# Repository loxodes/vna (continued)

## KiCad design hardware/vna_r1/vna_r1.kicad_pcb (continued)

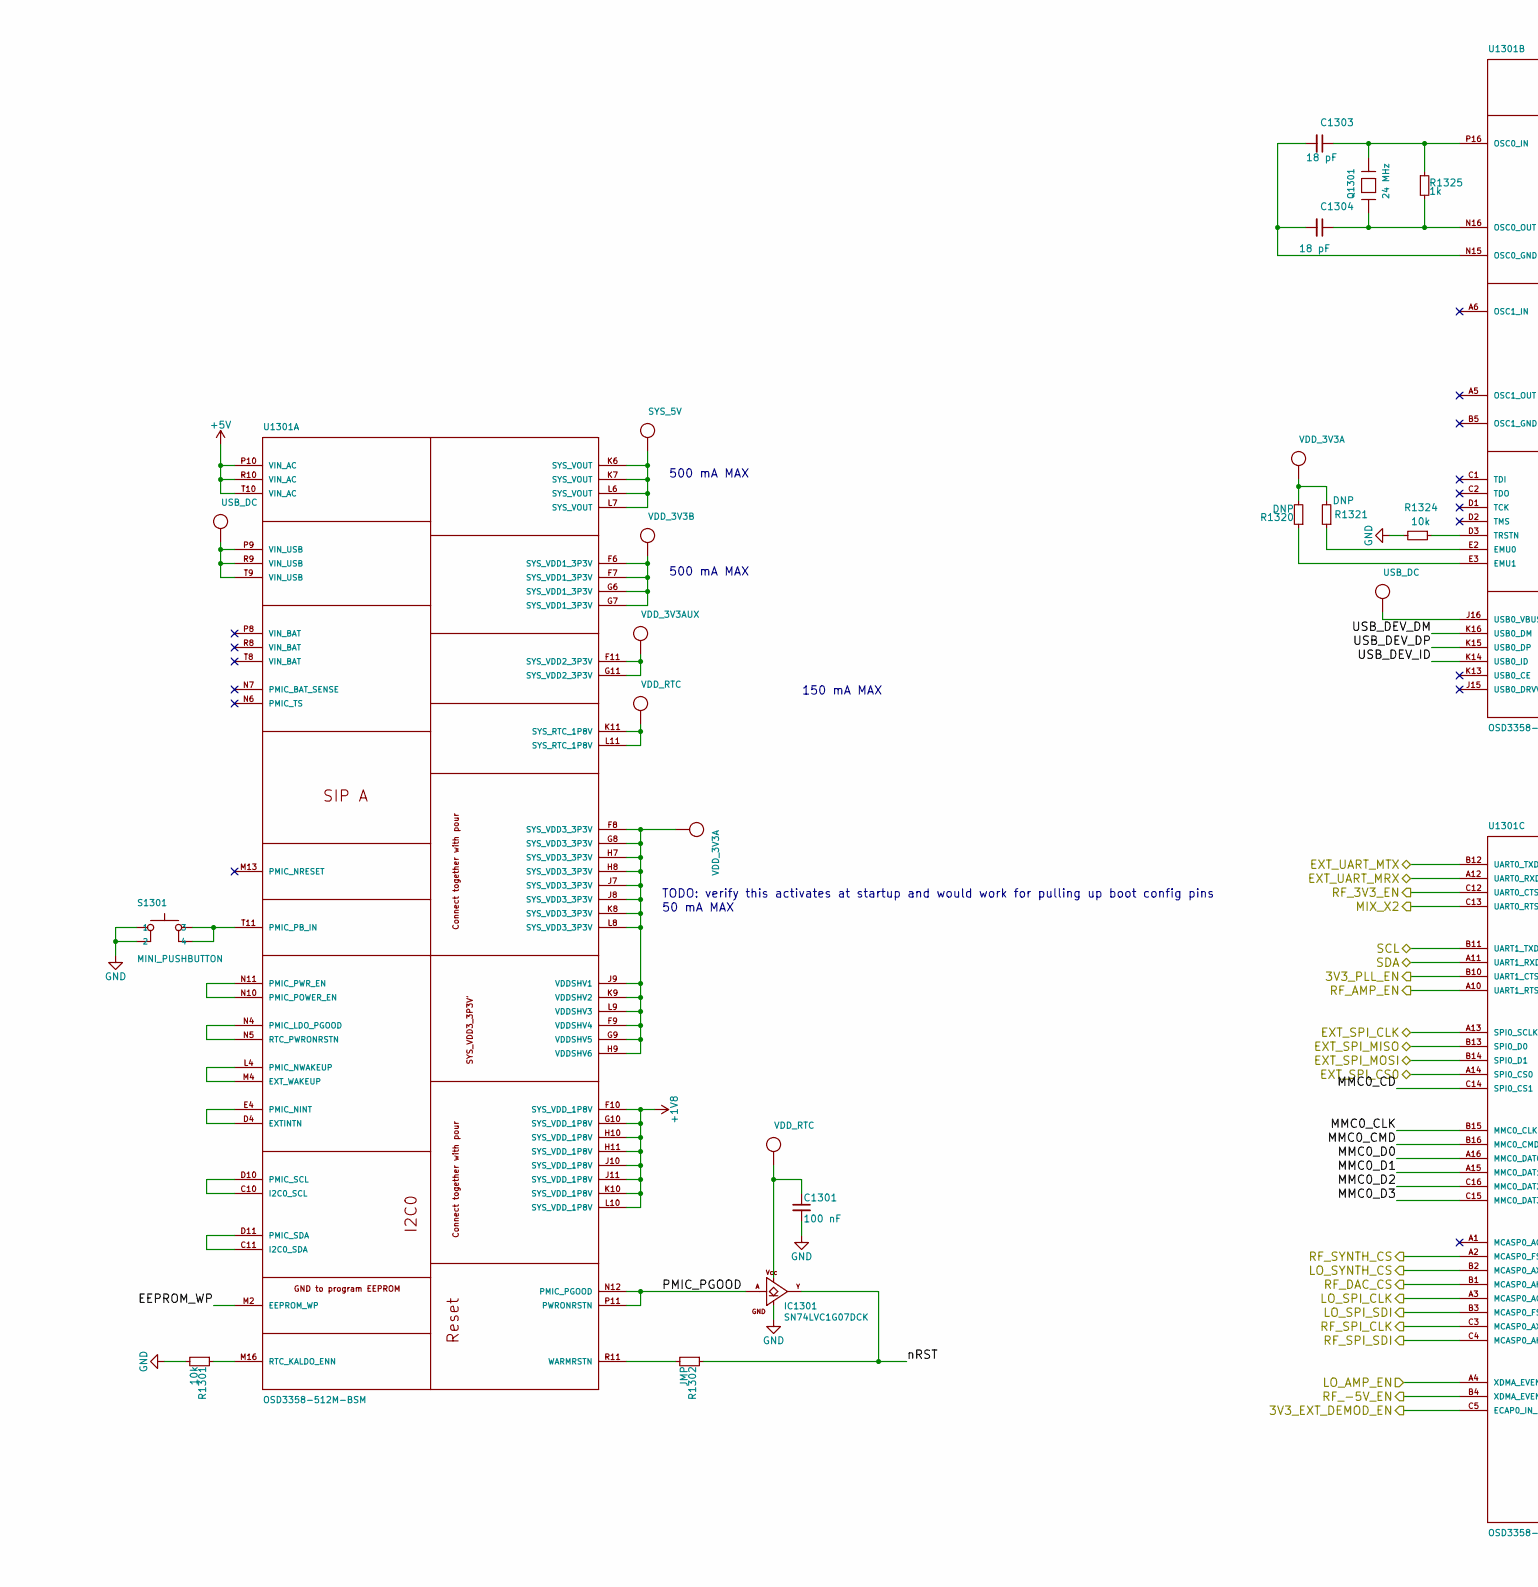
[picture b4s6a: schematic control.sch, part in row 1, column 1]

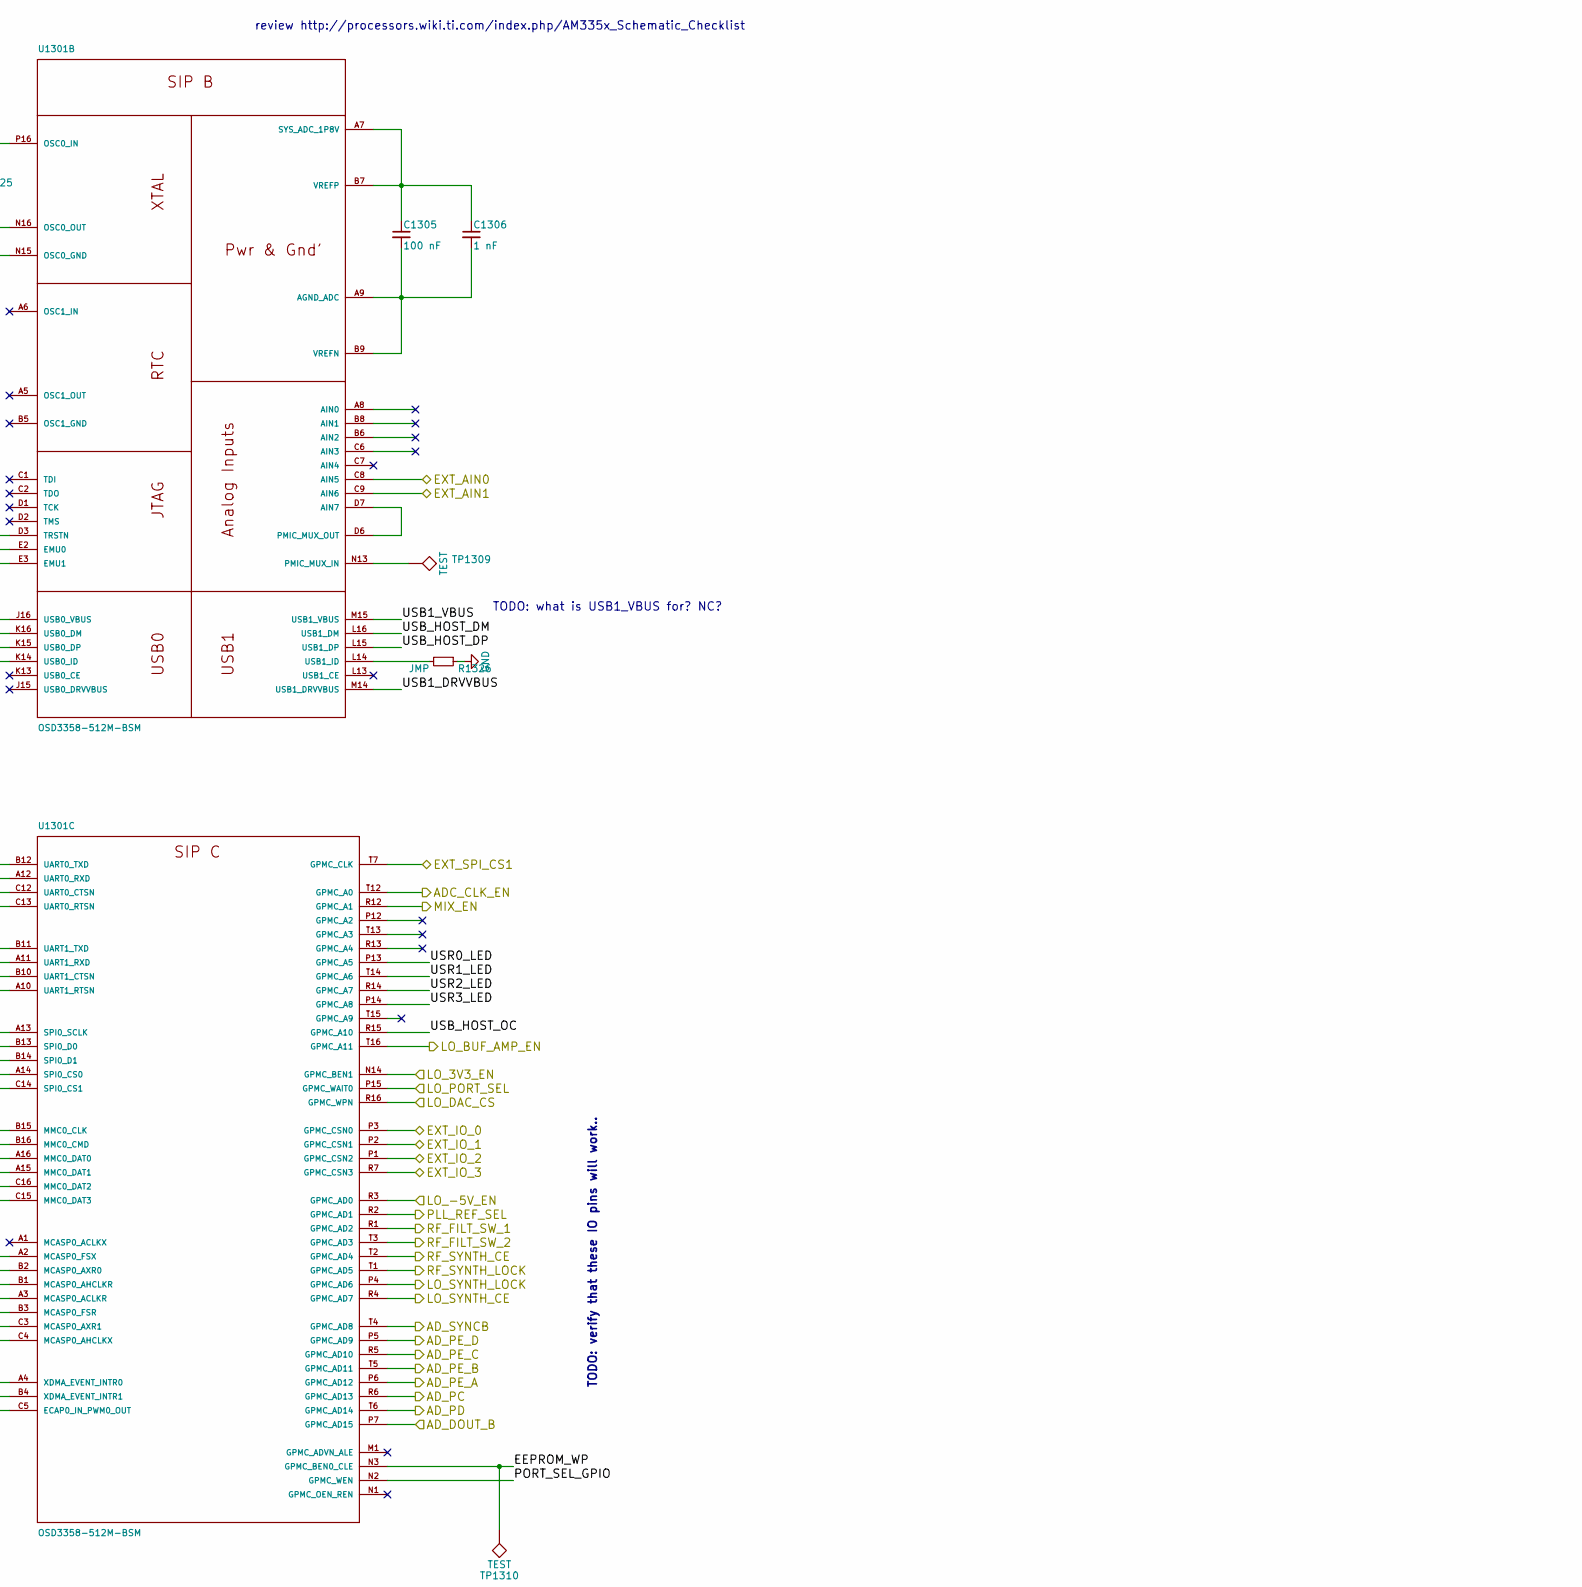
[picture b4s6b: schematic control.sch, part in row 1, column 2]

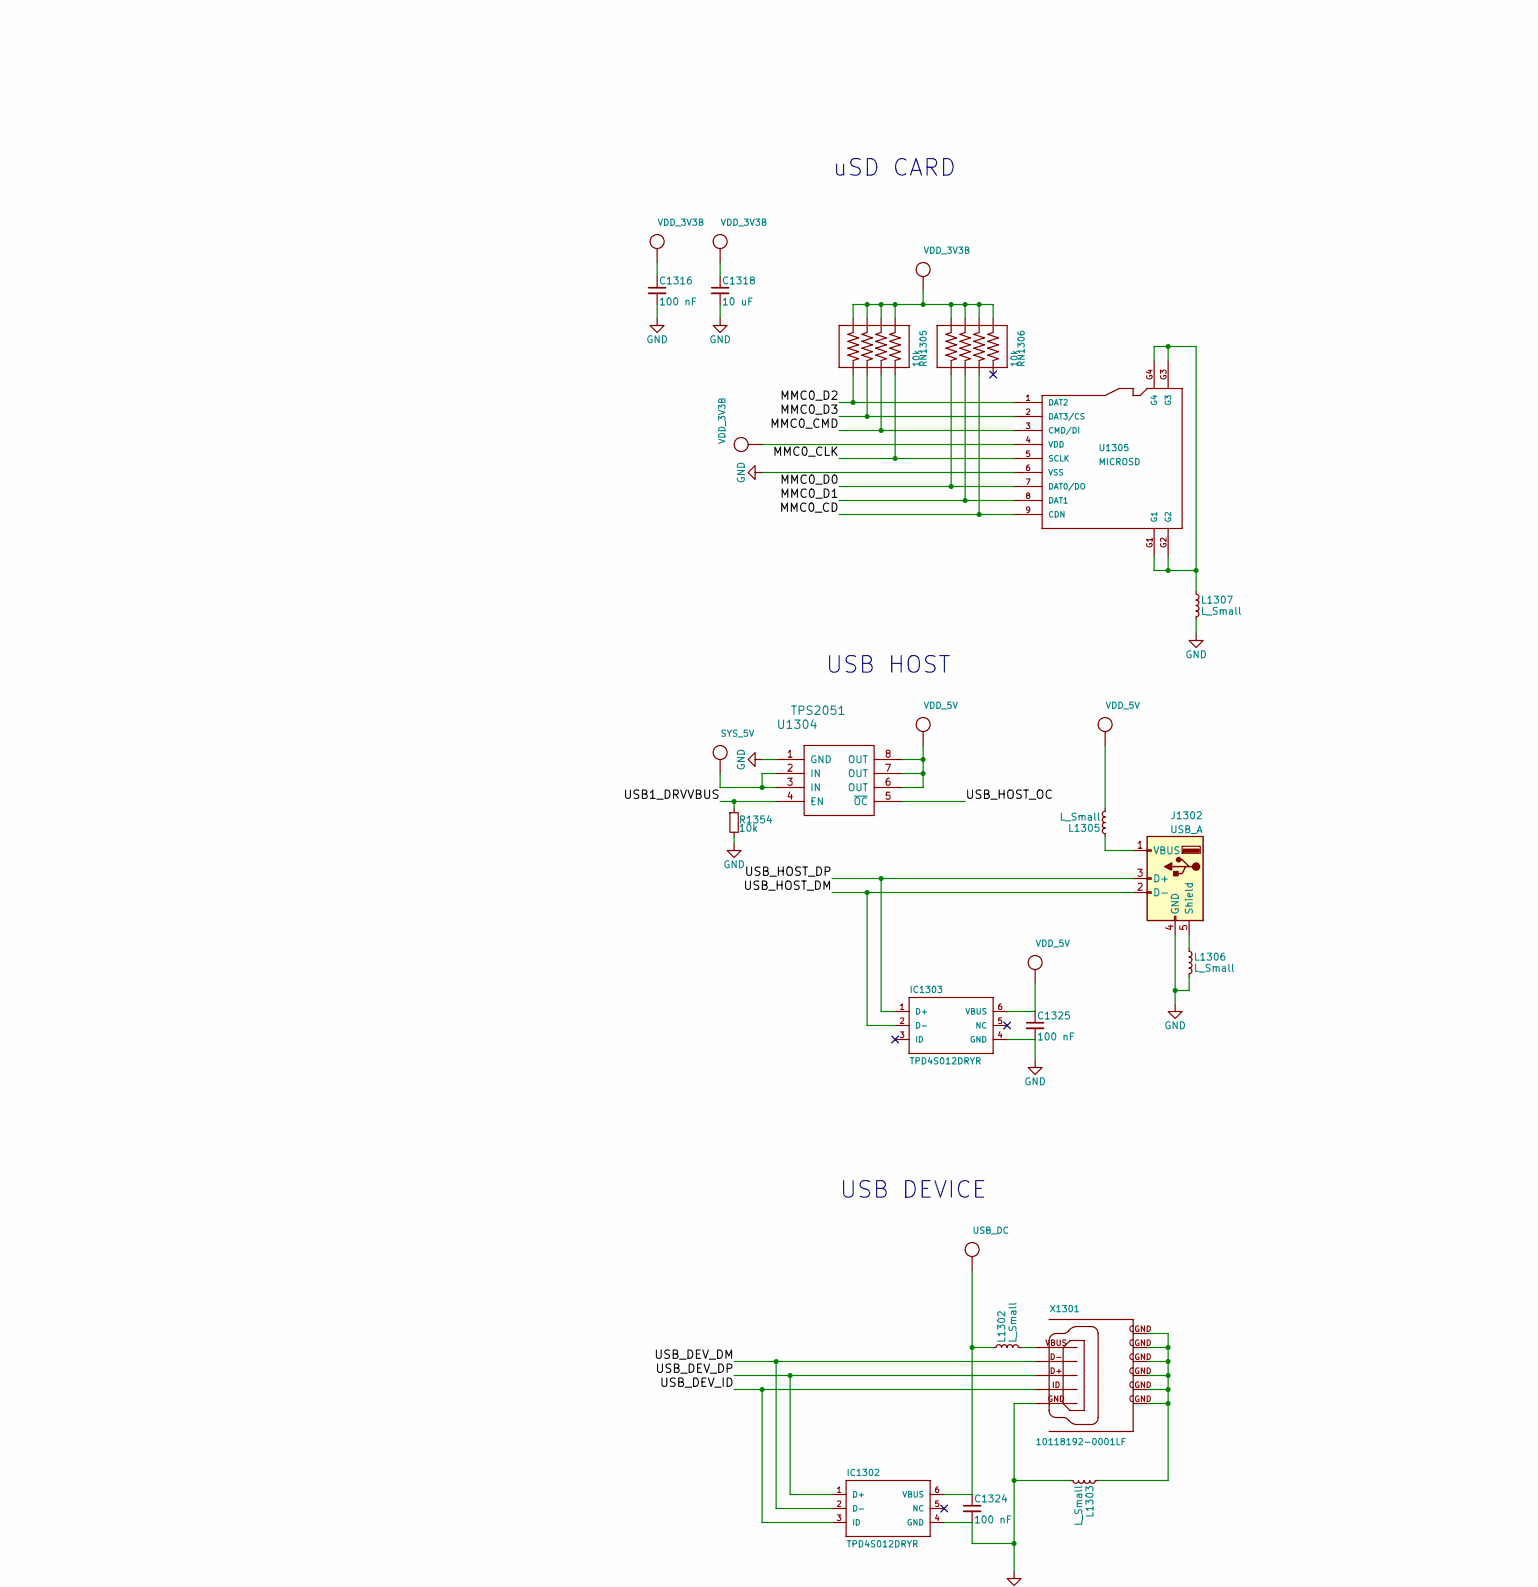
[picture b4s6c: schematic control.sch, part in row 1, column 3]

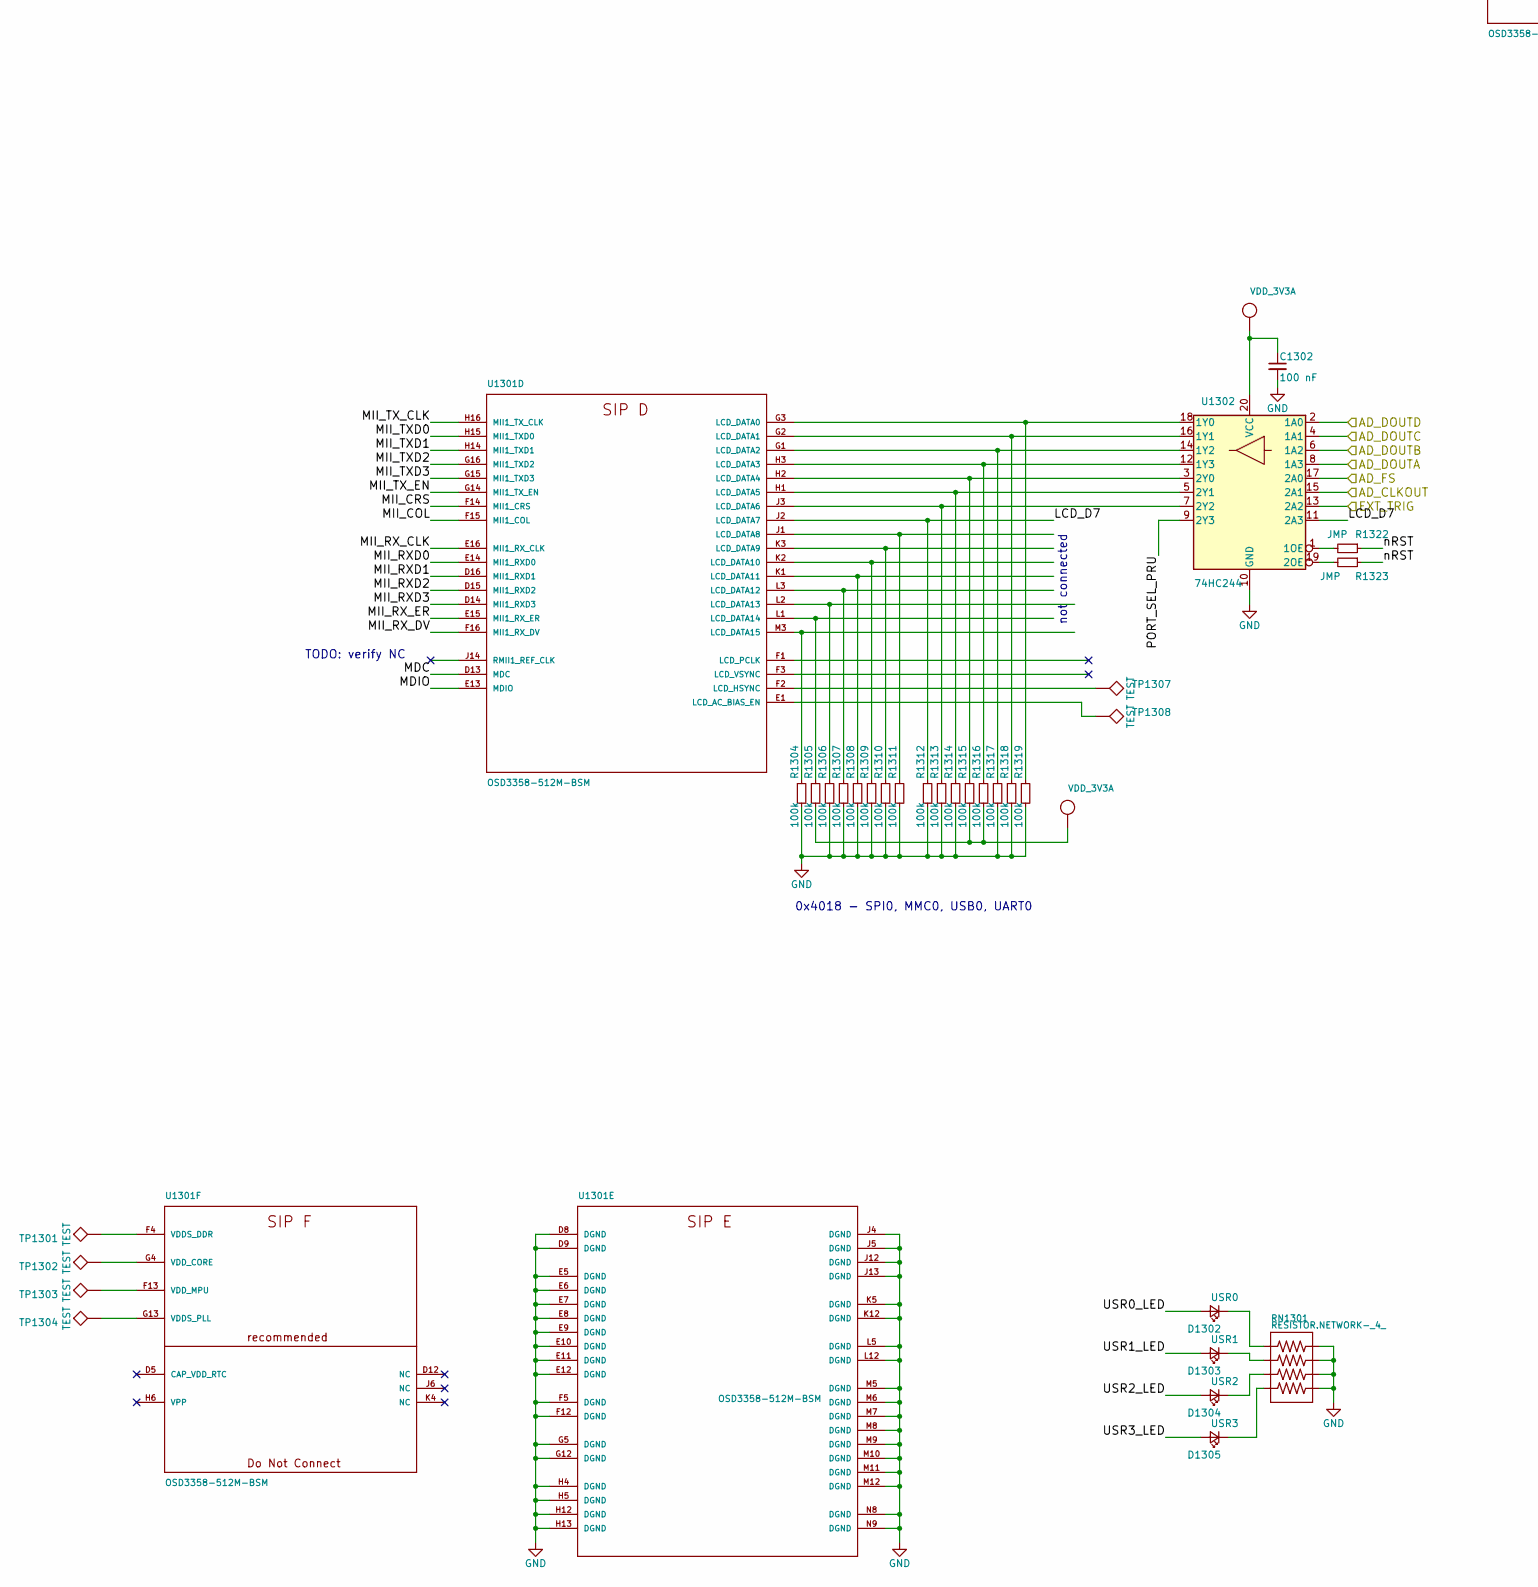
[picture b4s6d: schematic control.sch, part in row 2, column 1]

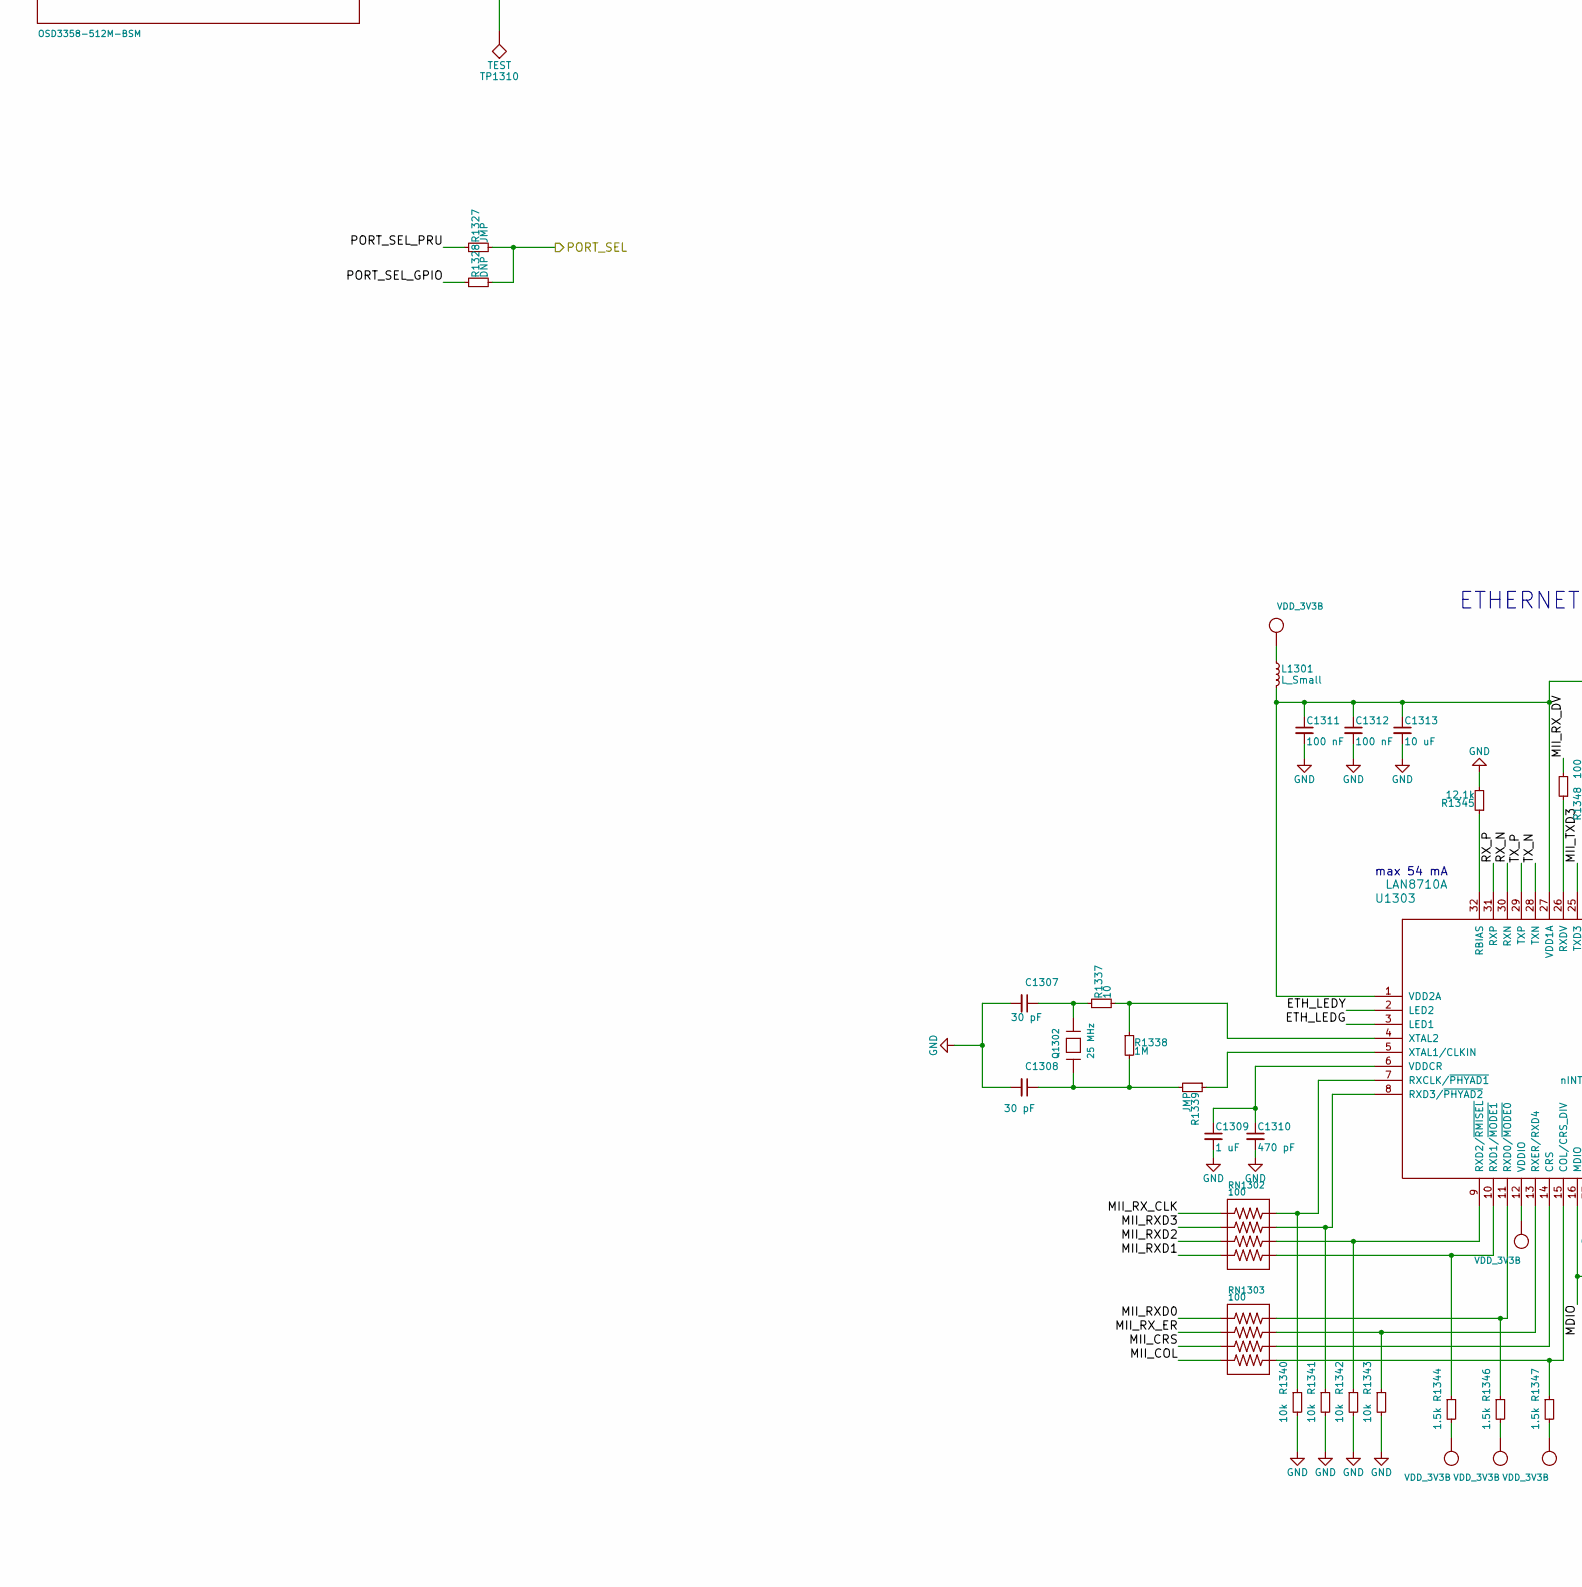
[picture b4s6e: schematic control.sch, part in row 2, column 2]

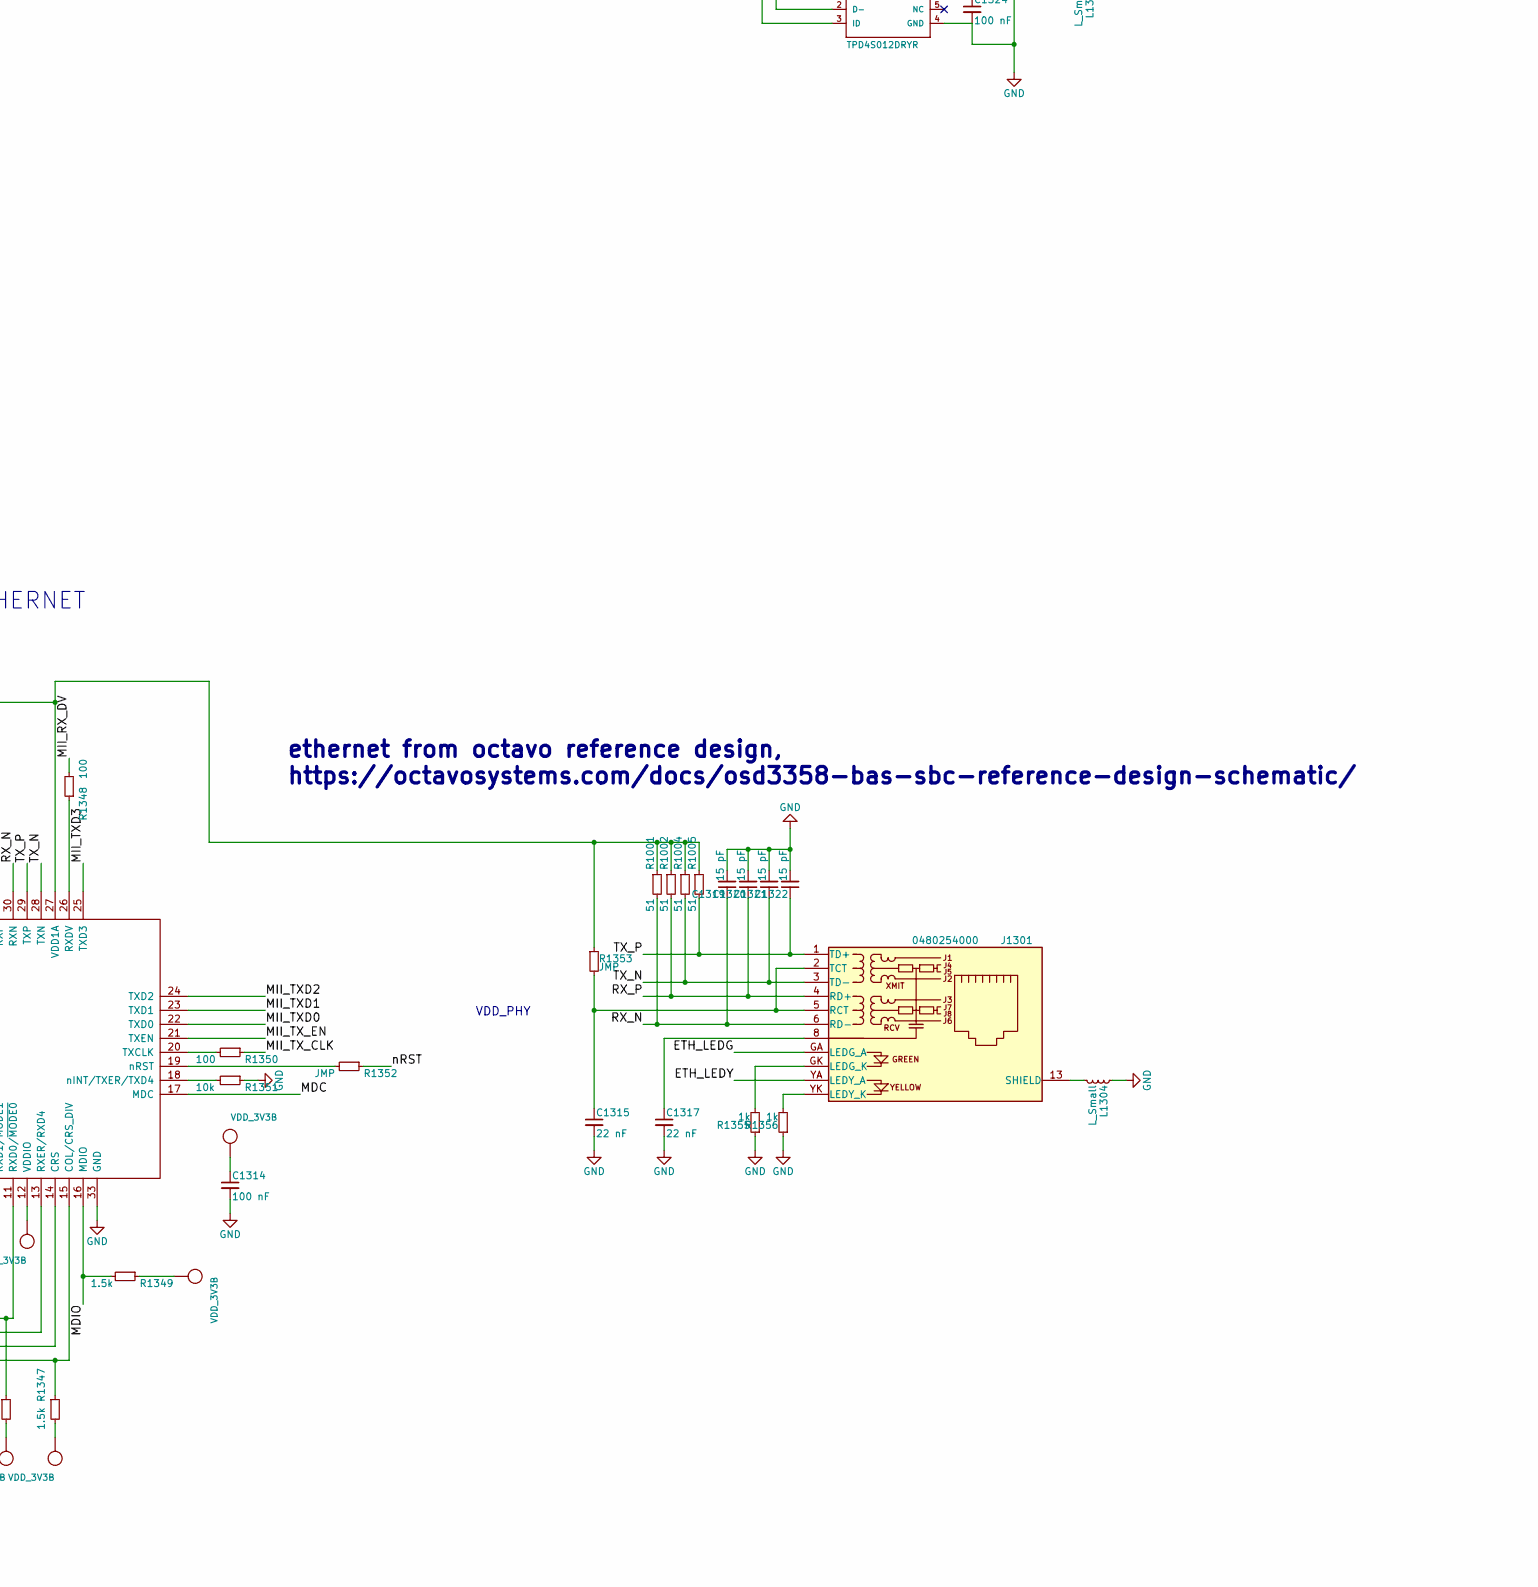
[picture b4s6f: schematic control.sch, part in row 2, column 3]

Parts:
C1301, C1302, C1305, C1311, C1312, C1314, C1316, C1324, C1325: 100 nF; C_0402
C1303, C1304: 18 pF; C_0402
C1306: 1 nF; C_0402
C1307, C1308: 30 pF; C_0402
C1309: 1 uF; C_0402
C1310: 470 pF; C_0402
C1313, C1318: 10 uF; C_0603
C1315, C1317: 22 nF; C_0402
C1319, C1320, C1321, C1322: 15 pF; C_0402
D1302: USR0; LED_0603
D1303: USR1; LED_0603
D1304: USR2; LED_0603
D1305: USR3; LED_0603
IC1301: SN74LVC1G07DCK; SC-70-5
IC1302, IC1303: TPD4S012DRYR; SON-6(TI)-DRY
J1301: 0480254000; RJ45_TRANSFO
J1302: USB_A
L1301, L1303, L1304, L1306, L1307: L_Small; R_0402
L1302, L1305: L_Small; R_0805
Q1301: 24 MHz; CRYSTAL_5X3.2MM
Q1302: 25 MHz; CRYSTAL_5X3.2MM
R1001, R1002, R1004, R1005: 51; R_0402
R1301, R1324, R1340, R1341, R1342, R1343, R1351, R1354: 10k; R_0402
R1302, R1322, R1323, R1326, R1327, R1339, R1352, R1353: JMP; R_0402
R1304, R1305, R1306, R1307, R1308, R1309, R1310, R1311, R1312, R1313, R1314, R1315, R1316, R1317, R1318, R1319: 100k; R_0402
R1320, R1321, R1328: DNP; R_0402
R1325, R1355, R1356: 1k; R_0402
R1337: 10; R_0402
R1338: 1M; R_0402
R1344, R1346, R1347, R1349: 1.5k; R_0402
R1345: 12.1k; R_0402
R1348, R1350: 100; R_0402
RN1301: RESISTOR.NETWORK-_4_; RN0804
RN1302, RN1303: 100; RN0804
RN1305, RN1306: 10k; RN0804
S1301: MINI_PUSHBUTTON
TP1301, TP1302, TP1303, TP1304, TP1307, TP1308, TP1309, TP1310: TEST; TP07R
U1301: OSD3358-512M-BSM; OSD335X-BGA-256
U1302: 74HC244; TSSOP-20_4.4x6.5mm_Pitch0.65mm
U1303: LAN8710A; QFN-32-1EP_5x5mm_Pitch0.5mm
U1304: TPS2051; SOIC-8_3.9x4.9mm_Pitch1.27mm
U1305: MICROSD
X1301: 10118192-0001LF; 10118192-0001LF(MICRO-USB-B-AMPHENOL-FCI)

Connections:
+1V8: U1301.F10 (SYS_VDD_1P8V), U1301.G10 (SYS_VDD_1P8V), U1301.H10 (SYS_VDD_1P8V), U1301.H11 (SYS_VDD_1P8V), U1301.J10 (SYS_VDD_1P8V), U1301.J11 (SYS_VDD_1P8V), U1301.K10 (SYS_VDD_1P8V), U1301.L10 (SYS_VDD_1P8V)
+5V: U1301.P10 (VIN_AC), U1301.R10 (VIN_AC), U1301.T10 (VIN_AC); also elsewhere on the board
/3V3_DEMOD_EXT_EN: U1301.C5 (ECAP0_IN_PWM0_OUT); also elsewhere on the board
/3V3_PLL_EN: U1301.B10 (UART1_CTSN); also elsewhere on the board
/ADC_CLK_EN: U1301.T12 (GPMC_A0); also elsewhere on the board
/AD_CLKOUT: U1302.15 (2A1); also elsewhere on the board
/AD_DOUTA_A: U1302.8 (1A3); also elsewhere on the board
/AD_DOUTA_B: U1302.6 (1A2); also elsewhere on the board
/AD_DOUTA_C: U1302.4 (1A1); also elsewhere on the board
/AD_DOUTA_D: U1302.2 (1A0); also elsewhere on the board
/AD_DOUTB: U1301.P7 (GPMC_AD15); also elsewhere on the board
/AD_FS: U1302.17 (2A0); also elsewhere on the board
/AD_PC: U1301.R6 (GPMC_AD13); also elsewhere on the board
/AD_PD: U1301.T6 (GPMC_AD14); also elsewhere on the board
/AD_PE_A: U1301.P6 (GPMC_AD12); also elsewhere on the board
/AD_PE_B: U1301.T5 (GPMC_AD11); also elsewhere on the board
/AD_PE_C: U1301.R5 (GPMC_AD10); also elsewhere on the board
/AD_PE_D: U1301.P5 (GPMC_AD9); also elsewhere on the board
/AD_SYNCB: U1301.T4 (GPMC_AD8); also elsewhere on the board
/EXT_AIN0: U1301.C8 (AIN5); also elsewhere on the board
/EXT_AIN1: U1301.C9 (AIN6); also elsewhere on the board
/EXT_IO_0: U1301.P3 (GPMC_CSN0); also elsewhere on the board
/EXT_IO_1: U1301.P2 (GPMC_CSN1); also elsewhere on the board
/EXT_IO_2: U1301.P1 (GPMC_CSN2); also elsewhere on the board
/EXT_IO_3: U1301.R7 (GPMC_CSN3); also elsewhere on the board
/EXT_SPI_CLK: U1301.B14 (SPI0_D1); also elsewhere on the board
/EXT_SPI_CS0: U1301.A14 (SPI0_CS0); also elsewhere on the board
/EXT_SPI_CS1: U1301.T7 (GPMC_CLK); also elsewhere on the board
/EXT_SPI_MISO: U1301.B13 (SPI0_D0); also elsewhere on the board
/EXT_SPI_MOSI: U1301.A13 (SPI0_SCLK); also elsewhere on the board
/EXT_TRIG: U1302.13 (2A2); also elsewhere on the board
/EXT_UART_MRX: U1301.A12 (UART0_RXD); also elsewhere on the board
/EXT_UART_MTX: U1301.B12 (UART0_TXD); also elsewhere on the board
/LO_3V3_EN: U1301.N14 (GPMC_BEN1); also elsewhere on the board
/LO_-5V_EN: U1301.R3 (GPMC_AD0); also elsewhere on the board
/LO_AMP_EN: U1301.A4 (XDMA_EVENT_INTR0); also elsewhere on the board
/LO_BUF_AMP_EN: U1301.T16 (GPMC_A11); also elsewhere on the board
/LO_DAC_CS: U1301.R16 (GPMC_WPN); also elsewhere on the board
/LO_PORT_SEL: U1301.P15 (GPMC_WAIT0); also elsewhere on the board
/LO_SPI_CLK: U1301.A3 (MCASP0_ACLKR); also elsewhere on the board
/LO_SPI_SDI: U1301.B3 (MCASP0_FSR); also elsewhere on the board
/LO_SYNTH_CE: U1301.R4 (GPMC_AD7); also elsewhere on the board
/LO_SYNTH_CS: U1301.B2 (MCASP0_AXR0); also elsewhere on the board
/LO_SYNTH_LOCK: U1301.P4 (GPMC_AD6); also elsewhere on the board
/MIX_EN: U1301.R12 (GPMC_A1); also elsewhere on the board
/MIX_X2: U1301.C13 (UART0_RTSN); also elsewhere on the board
/PLL_REF_SEL: U1301.R2 (GPMC_AD1); also elsewhere on the board
/RF_3V3_EN: U1301.C12 (UART0_CTSN); also elsewhere on the board
/RF_-5V_EN: U1301.B4 (XDMA_EVENT_INTR1); also elsewhere on the board
/RF_AMP_EN: U1301.A10 (UART1_RTSN); also elsewhere on the board
/RF_DAC_CS: U1301.B1 (MCASP0_AHCLKR); also elsewhere on the board
/RF_FILT_SW_1: U1301.R1 (GPMC_AD2); also elsewhere on the board
/RF_FILT_SW_2: U1301.T3 (GPMC_AD3); also elsewhere on the board
/RF_PORT_SEL: R1327.2, R1328.2; also elsewhere on the board
/RF_SPI_CLK: U1301.C3 (MCASP0_AXR1); also elsewhere on the board
/RF_SPI_SDI: U1301.C4 (MCASP0_AHCLKX); also elsewhere on the board
/RF_SYNTH_CE: U1301.T2 (GPMC_AD4); also elsewhere on the board
/RF_SYNTH_CS: U1301.A2 (MCASP0_FSX); also elsewhere on the board
/RF_SYNTH_LOCK: U1301.T1 (GPMC_AD5); also elsewhere on the board
/SCL: U1301.B11 (UART1_TXD); also elsewhere on the board
/SDA: U1301.A11 (UART1_RXD); also elsewhere on the board
/control/EEPROM_WP: TP1310.1, U1301.M2 (EEPROM_WP), U1301.N3 (GPMC_BEN0_CLE)
/control/ETH_LEDG: J1301.GA (LEDG_A), U1303.3 (LED1)
/control/ETH_LEDY: J1301.YA (LEDY_A), U1303.2 (LED2)
/control/LCD_D7: R1312.1, U1301.J2 (LCD_DATA7), U1302.11 (2A3)
/control/MDC: U1301.D13 (MDC), U1303.17 (MDC)
/control/MDIO: R1349.2, U1301.E13 (MDIO), U1303.16 (MDIO)
/control/MII_COL: RN1303.4, U1301.F15 (MII1_COL)
/control/MII_CRS: RN1303.3, U1301.F14 (MII1_CRS)
/control/MII_RXD0: RN1303.1, U1301.E14 (MII1_RXD0)
/control/MII_RXD1: RN1302.4, U1301.D16 (MII1_RXD1)
/control/MII_RXD2: RN1302.3, U1301.D15 (MII1_RXD2)
/control/MII_RXD3: RN1302.2, U1301.D14 (MII1_RXD3)
/control/MII_RX_CLK: RN1302.1, U1301.E16 (MII1_RX_CLK)
/control/MII_RX_DV: R1348.2, U1301.F16 (MII1_RX_DV)
/control/MII_RX_ER: RN1303.2, U1301.E15 (MII1_RX_ER)
/control/MII_TXD0: U1301.H15 (MII1_TXD0), U1303.22 (TXD0)
/control/MII_TXD1: U1301.H14 (MII1_TXD1), U1303.23 (TXD1)
/control/MII_TXD2: U1301.G16 (MII1_TXD2), U1303.24 (TXD2)
/control/MII_TXD3: U1301.G15 (MII1_TXD3), U1303.25 (TXD3)
/control/MII_TX_CLK: R1350.1, U1301.H16 (MII1_TX_CLK)
/control/MII_TX_EN: U1301.G14 (MII1_TX_EN), U1303.21 (TXEN)
/control/MMC0_CD: RN1306.2, U1301.C14 (SPI0_CS1), U1305.9 (CDN)
/control/MMC0_CLK: RN1305.1, U1301.B15 (MMC0_CLK), U1305.5 (SCLK)
/control/MMC0_CMD: RN1305.2, U1301.B16 (MMC0_CMD), U1305.3 (CMD/DI)
/control/MMC0_D0: RN1306.4, U1301.A16 (MMC0_DAT0), U1305.7 (DAT0/DO)
/control/MMC0_D1: RN1306.3, U1301.A15 (MMC0_DAT1), U1305.8 (DAT1)
/control/MMC0_D2: RN1305.4, U1301.C16 (MMC0_DAT2), U1305.1 (DAT2)
/control/MMC0_D3: RN1305.3, U1301.C15 (MMC0_DAT3), U1305.2 (DAT3/CS)
/control/PMIC_PGOOD: IC1301.2 (A), U1301.N12 (PMIC_PGOOD), U1301.P11 (PWRONRSTN)
/control/PORT_SEL_GPIO: R1328.1, U1301.N2 (GPMC_WEN)
/control/PORT_SEL_PRU: R1327.1, U1302.9 (2Y3)
/control/RX_N: C1319.1, J1301.6 (RD-), R1001.2, U1303.30 (RXN)
/control/RX_P: C1320.1, J1301.4 (RD+), R1002.2, U1303.31 (RXP)
/control/TX_N: C1321.1, J1301.3 (TD-), R1004.2, U1303.28 (TXN)
/control/TX_P: C1322.1, J1301.1 (TD+), R1005.2, U1303.29 (TXP)
/control/USB1_DRVVBUS: R1354.1, U1301.M14 (USB1_DRVVBUS), U1304.4 (EN)
/control/USB_DEV_DM: IC1302.2 (D-), U1301.K16 (USB0_DM), X1301.D-
/control/USB_DEV_DP: IC1302.1 (D+), U1301.K15 (USB0_DP), X1301.D+
/control/USB_DEV_ID: IC1302.3 (ID), U1301.K14 (USB0_ID), X1301.ID
/control/USB_HOST_DM: IC1303.2 (D-), J1302.2 (D-), U1301.L16 (USB1_DM)
/control/USB_HOST_DP: IC1303.1 (D+), J1302.3 (D+), U1301.L15 (USB1_DP)
/control/USB_HOST_OC: U1301.R15 (GPMC_A10), U1304.5 (~OC)
/control/USR0_LED: D1302.2 (A), U1301.P13 (GPMC_A5)
/control/USR1_LED: D1303.2 (A), U1301.T14 (GPMC_A6)
/control/USR2_LED: D1304.2 (A), U1301.R14 (GPMC_A7)
/control/USR3_LED: D1305.2 (A), U1301.P14 (GPMC_A8)
/control/nRST: IC1301.4 (Y), R1302.1, R1322.1, R1323.1, R1352.1
GND: C1301.2, C1302.2, C1307.2, C1308.2, C1309.2, C1310.2, C1311.2, C1312.2, C1313.2, C1314.2, C1315.2, C1316.2, C1317.2, C1318.2, C1319.2, C1320.2, C1321.2, C1322.2, C1324.2, C1325.2, IC1301.3 (GND), IC1302.4 (GND), IC1303.4 (GND), J1302.4 (GND), L1303.2, L1304.1, L1306.2, L1307.2, R1301.2, R1304.2, R1306.2, R1307.2, R1308.2, R1309.2, R1310.2, R1311.2, R1312.2, R1313.2, R1314.2, R1317.2, R1318.2, R1319.2, R1324.2, R1326.1, R1340.2, R1341.2, R1342.2, R1343.2, R1345.2, R1351.1, R1354.2, R1355.1, R1356.1, RN1301.5, RN1301.6, RN1301.7, RN1301.8, S1301.1, S1301.2, U1301.D8 (DGND), U1301.D9 (DGND), U1301.E5 (DGND), U1301.E6 (DGND), U1301.E7 (DGND), U1301.E8 (DGND), U1301.E9 (DGND), U1301.E10 (DGND), U1301.E11 (DGND), U1301.E12 (DGND), U1301.F5 (DGND), U1301.F12 (DGND), U1301.G5 (DGND), U1301.G12 (DGND), U1301.H4 (DGND), U1301.H5 (DGND), U1301.H12 (DGND), U1301.H13 (DGND), U1301.J4 (DGND), U1301.J5 (DGND), U1301.J12 (DGND), U1301.J13 (DGND), U1301.K5 (DGND), U1301.K12 (DGND), U1301.L5 (DGND), U1301.L12 (DGND), U1301.M5 (DGND), U1301.M6 (DGND), U1301.M7 (DGND), U1301.M8 (DGND), U1301.M9 (DGND), U1301.M10 (DGND), U1301.M11 (DGND), U1301.M12 (DGND), U1301.N8 (DGND), U1301.N9 (DGND), U1302.10 (GND), U1303.33 (GND), U1304.1 (GND), U1305.6 (VSS), X1301.GND; also elsewhere on the board
unnamed: C1303.1, Q1301.2, R1325.1, U1301.P16 (OSC0_IN)
unnamed: C1303.2, C1304.2, U1301.N15 (OSC0_GND)
unnamed: C1304.1, Q1301.1, R1325.2, U1301.N16 (OSC0_OUT)
unnamed: C1305.1, C1306.1, U1301.A7 (SYS_ADC_1P8V), U1301.B7 (VREFP)
unnamed: C1305.2, C1306.2, U1301.A9 (AGND_ADC), U1301.B9 (VREFN)
unnamed: C1307.1, Q1302.2, R1337.1
unnamed: C1308.1, Q1302.1, R1338.2, R1339.2
unnamed: C1309.1, C1310.1, U1303.6 (VDDCR)
unnamed: C1311.1, C1312.1, C1313.1, L1301.2, R1001.1, R1002.1, R1004.1, R1005.1, R1353.1, U1303.1 (VDD2A), U1303.27 (VDD1A)
unnamed: C1315.1, J1301.2 (TCT), J1301.5 (RCT), R1353.2
unnamed: C1317.1, J1301.8
unnamed: D1302.1 (K), RN1301.1
unnamed: D1303.1 (K), RN1301.2
unnamed: D1304.1 (K), RN1301.3
unnamed: D1305.1 (K), RN1301.4
unnamed: J1301.13 (SHIELD), L1304.2
unnamed: J1301.GK (LEDG_K), R1355.2
unnamed: J1301.YK (LEDY_K), R1356.2
unnamed: J1302.1 (VBUS), L1305.1
unnamed: J1302.5 (Shield), L1306.1
unnamed: L1302.2, X1301.VBUS
unnamed: L1303.1, X1301.CGND (SGND1)
unnamed: L1307.1, U1305.G1, U1305.G2, U1305.G3, U1305.G4
unnamed: R1301.1, U1301.M16 (RTC_KALDO_ENN)
unnamed: R1302.2, U1301.R11 (WARMRSTN)
unnamed: R1304.1, U1301.M3 (LCD_DATA15)
unnamed: R1305.1, U1301.L1 (LCD_DATA14)
unnamed: R1306.1, U1301.L2 (LCD_DATA13)
unnamed: R1307.1, U1301.L3 (LCD_DATA12)
unnamed: R1308.1, U1301.K1 (LCD_DATA11)
unnamed: R1309.1, U1301.K2 (LCD_DATA10)
unnamed: R1310.1, U1301.K3 (LCD_DATA9)
unnamed: R1311.1, U1301.J1 (LCD_DATA8)
unnamed: R1313.1, U1301.J3 (LCD_DATA6), U1302.7 (2Y2)
unnamed: R1314.1, U1301.H1 (LCD_DATA5), U1302.5 (2Y1)
unnamed: R1315.1, U1301.H2 (LCD_DATA4), U1302.3 (2Y0)
unnamed: R1316.1, U1301.H3 (LCD_DATA3), U1302.12 (1Y3)
unnamed: R1317.1, U1301.G1 (LCD_DATA2), U1302.14 (1Y2)
unnamed: R1318.1, U1301.G2 (LCD_DATA1), U1302.16 (1Y1)
unnamed: R1319.1, U1301.G3 (LCD_DATA0), U1302.18 (1Y0)
unnamed: R1320.1, U1301.E3 (EMU1)
unnamed: R1321.1, U1301.E2 (EMU0)
unnamed: R1322.2, U1302.1 (1OE)
unnamed: R1323.2, U1302.19 (2OE)
unnamed: R1324.1, U1301.D3 (TRSTN)
unnamed: R1326.2, U1301.L14 (USB1_ID)
unnamed: R1337.2, R1338.1, U1303.4 (XTAL2)
unnamed: R1339.1, U1303.5 (XTAL1/CLKIN)
unnamed: R1340.1, RN1302.8, U1303.7 (RXCLK/~PHYAD1)
unnamed: R1341.1, RN1302.7, U1303.8 (RXD3/~PHYAD2)
unnamed: R1342.1, RN1302.6, U1303.9 (RXD2/~RMISEL)
unnamed: R1343.1, RN1303.7, U1303.13 (RXER/RXD4)
unnamed: R1344.1, RN1302.5, U1303.10 (RXD1/~MODE1)
unnamed: R1345.1, U1303.32 (RBIAS)
unnamed: R1346.1, RN1303.8, U1303.11 (RXD0/~MODE0)
unnamed: R1347.1, RN1303.5, U1303.15 (COL/CRS_DIV)
unnamed: R1348.1, U1303.26 (RXDV)
unnamed: R1350.2, U1303.20 (TXCLK)
unnamed: R1351.2, U1303.18 (nINT/TXER/TXD4)
unnamed: R1352.2, U1303.19 (nRST)
unnamed: RN1303.6, U1303.14 (CRS)
unnamed: S1301.3, S1301.4, U1301.T11 (PMIC_PB_IN)
unnamed: TP1301.1, U1301.F4 (VDDS_DDR)
unnamed: TP1302.1, U1301.G4 (VDD_CORE)
unnamed: TP1303.1, U1301.F13 (VDD_MPU)
unnamed: TP1304.1, U1301.G13 (VDDS_PLL)
unnamed: TP1307.1, U1301.F2 (LCD_HSYNC)
unnamed: TP1308.1, U1301.E1 (LCD_AC_BIAS_EN)
unnamed: TP1309.1, U1301.N13 (PMIC_MUX_IN)
unnamed: U1301.C10 (I2C0_SCL), U1301.D10 (PMIC_SCL)
unnamed: U1301.C11 (I2C0_SDA), U1301.D11 (PMIC_SDA)
unnamed: U1301.D4 (EXTINTN), U1301.E4 (PMIC_NINT)
unnamed: U1301.D6 (PMIC_MUX_OUT), U1301.D7 (AIN7)
unnamed: U1301.L4 (PMIC_NWAKEUP), U1301.M4 (EXT_WAKEUP)
unnamed: U1301.N4 (PMIC_LDO_PGOOD), U1301.N5 (RTC_PWRONRSTN)
unnamed: U1301.N10 (PMIC_POWER_EN), U1301.N11 (PMIC_PWR_EN)
SYS_5V: U1301.K6 (SYS_VOUT), U1301.K7 (SYS_VOUT), U1301.L6 (SYS_VOUT), U1301.L7 (SYS_VOUT), U1304.2 (IN), U1304.3 (IN)
USB_DC: C1324.1, IC1302.6 (VBUS), L1302.1, U1301.J16 (USB0_VBUS), U1301.P9 (VIN_USB), U1301.R9 (VIN_USB), U1301.T9 (VIN_USB)
VDD_3V3A: C1302.1, R1305.2, R1315.2, R1316.2, R1320.2, R1321.2, U1301.F8 (SYS_VDD3_3P3V), U1301.F9 (VDDSHV4), U1301.G8 (SYS_VDD3_3P3V), U1301.G9 (VDDSHV5), U1301.H7 (SYS_VDD3_3P3V), U1301.H8 (SYS_VDD3_3P3V), U1301.H9 (VDDSHV6), U1301.J7 (SYS_VDD3_3P3V), U1301.J8 (SYS_VDD3_3P3V), U1301.J9 (VDDSHV1), U1301.K8 (SYS_VDD3_3P3V), U1301.K9 (VDDSHV2), U1301.L8 (SYS_VDD3_3P3V), U1301.L9 (VDDSHV3), U1302.20 (VCC)
VDD_3V3AUX: U1301.F11 (SYS_VDD2_3P3V), U1301.G11 (SYS_VDD2_3P3V)
VDD_3V3B: C1314.1, C1316.1, C1318.1, L1301.1, R1344.2, R1346.2, R1347.2, R1349.1, RN1305.5, RN1305.6, RN1305.7, RN1305.8, RN1306.5, RN1306.6, RN1306.7, RN1306.8, U1301.F6 (SYS_VDD1_3P3V), U1301.F7 (SYS_VDD1_3P3V), U1301.G6 (SYS_VDD1_3P3V), U1301.G7 (SYS_VDD1_3P3V), U1303.12 (VDDIO), U1305.4 (VDD)
VDD_5V: C1325.1, IC1303.6 (VBUS), L1305.2, U1304.6 (OUT), U1304.7 (OUT), U1304.8 (OUT)
VDD_RTC: C1301.1, IC1301.5 (VCC), U1301.K11 (SYS_RTC_1P8V), U1301.L11 (SYS_RTC_1P8V)

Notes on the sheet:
ethernet from octavo reference design, https://octavosystems.com/docs/osd3358-bas-sbc-reference-design-schematic/
VDD_PHY
TODO: verify NC
500 mA MAX
50 mA MAX
150 mA MAX
max 54 mA
0x4018 - SPI0, MMC0, USB0, UART0
TODO: verify that these IO pins will work..
review http://processors.wiki.ti.com/index.php/AM335x_Schematic_Checklist
USB HOST
USB DEVICE
uSD CARD
ETHERNET
not connected
TODO: what is USB1_VBUS for? NC?
TODO: verify this activates at startup and would work for pulling up boot config pins
